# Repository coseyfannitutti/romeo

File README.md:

# ROMEO
 Staggered 40% QMK and VIA compatible keyboard pcb assembled with only through hole components, including USB Type-C

**[BOM, Build Guide, and Flashing Information](./doc)**

**Kits available at [cftkb.com](https://www.cftkb.com)**

**[Optional High Profile Lasercut Acrylic Case](./case)**

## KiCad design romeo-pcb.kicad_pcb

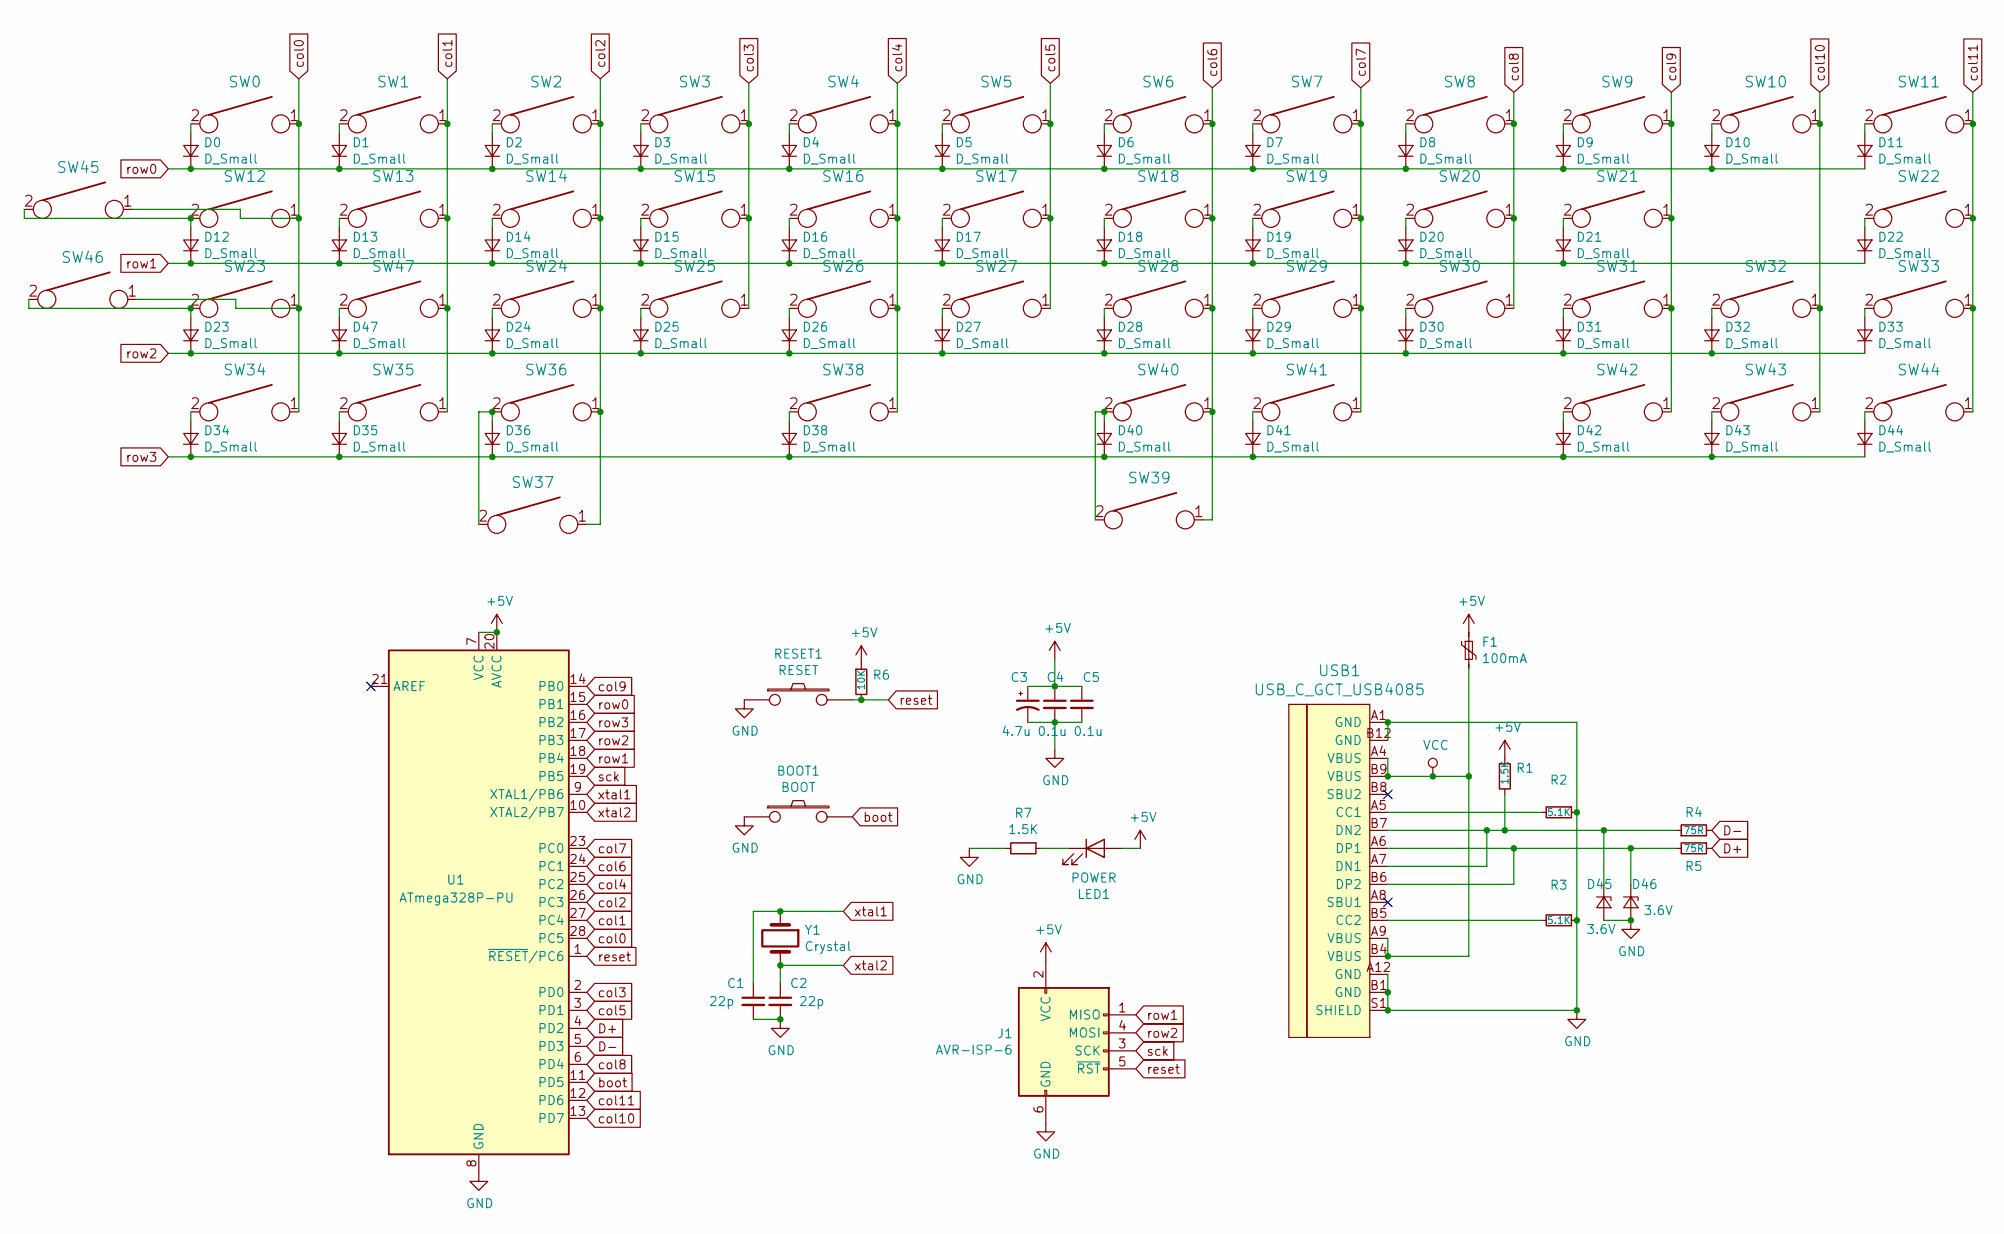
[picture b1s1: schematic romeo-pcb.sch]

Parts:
BOOT1: BOOT; SW_PUSH_6mm
C1, C2: 22p; C_Disc_D3.0mm_W1.6mm_P2.50mm
C3: 4.7u; CP_Radial_D4.0mm_P1.50mm
C4, C5: 0.1u; C_Disc_D4.3mm_W1.9mm_P5.00mm
D0, D1, D2, D3, D4, D5, D6, D7, D8, D9, D10, D11, D12, D13, D14, D15, D16, D17, D18, D19, D20, D21, D22, D23, D24, D25, D26, D27, D28, D29, D30, D31, D32, D33, D34, D35, D36, D38, D40, D41, D42, D43, D44, D47: D_Small; D_DO-35_SOD27_P5.08mm_Horizontal
D45, D46: 3.6V; D_DO-35_SOD27_P5.08mm_Horizontal
F1: 100mA; polyfuse_5.1mm
J1: AVR-ISP-6; AVR_ICSP_3x2
LED1: POWER; LED_D3.0mm
R1, R7: 1.5K; R_Axial_DIN0204_L3.6mm_D1.6mm_P5.08mm_Horizontal
R2, R3: 5.1K; R_Axial_DIN0204_L3.6mm_D1.6mm_P5.08mm_Horizontal
R4, R5: 75R; R_Axial_DIN0204_L3.6mm_D1.6mm_P5.08mm_Horizontal
R6: 10K; R_Axial_DIN0204_L3.6mm_D1.6mm_P5.08mm_Horizontal
RESET1: RESET; SW_PUSH_6mm
SW0, SW11: KEYSW; SW_Cherry_MX1A_1.50u_PCBNOSCREEN
SW1, SW2, SW3, SW4, SW5, SW6, SW7, SW8, SW9, SW10, SW13, SW14, SW15, SW16, SW17, SW18, SW19, SW20, SW21, SW24, SW25, SW26, SW27, SW28, SW29, SW30, SW31, SW32, SW35, SW36, SW39, SW40, SW43, SW47: KEYSW; SW_Cherry_MX1A_1.00u_PCB-NOSCREEN
SW12, SW33: KEYSW; SW_Cherry_MX1A_1.75u_PCBNOSCREEN
SW22, SW23, SW38: KEYSW; SW_Cherry_MX1A_2.25u_PCBNOSCREEN
SW34, SW37, SW42, SW44, SW45, SW46: KEYSW; SW_Cherry_MX1A_1.25u_PCBNOSCREEN
SW41: KEYSW; SW_Cherry_MX1A_2.75u_PCB_NOSCREEN
U1: ATmega328P-PU; DIP-28_W7.62mm
USB1: USB_C_GCT_USB4085
Y1: Crystal; Crystal_HC49-4H_Vertical

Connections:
+5V: C3.1, C4.1, C5.1, F1.1, J1.2 (VCC), LED1.2 (A), R1.1, R6.1, U1.7 (VCC), U1.20 (AVCC)
D+: R5.1, U1.4 (PD2)
D-: R4.2, U1.5 (PD3)
GND: BOOT1.1, C1.2, C2.2, C3.2, C4.2, C5.2, D45.2 (A), D46.2 (A), J1.6 (GND), R2.1, R3.1, R7.2, RESET1.1, U1.8 (GND), U1.22 (GND), USB1.A1 (GND), USB1.A12 (GND), USB1.B1 (GND), USB1.B12 (GND), USB1.S1 (SHIELD)
unnamed: D0.2 (A), SW0.2
unnamed: D1.2 (A), SW1.2
unnamed: D2.2 (A), SW2.2
unnamed: D3.2 (A), SW3.2
unnamed: D4.2 (A), SW4.2
unnamed: D5.2 (A), SW5.2
unnamed: D6.2 (A), SW6.2
unnamed: D7.2 (A), SW7.2
unnamed: D8.2 (A), SW8.2
unnamed: D9.2 (A), SW9.2
unnamed: D10.2 (A), SW10.2
unnamed: D11.2 (A), SW11.2
unnamed: D12.2 (A), SW12.2, SW45.2
unnamed: D13.2 (A), SW13.2
unnamed: D14.2 (A), SW14.2
unnamed: D15.2 (A), SW15.2
unnamed: D16.2 (A), SW16.2
unnamed: D17.2 (A), SW17.2
unnamed: D18.2 (A), SW18.2
unnamed: D19.2 (A), SW19.2
unnamed: D20.2 (A), SW20.2
unnamed: D21.2 (A), SW21.2
unnamed: D22.2 (A), SW22.2
unnamed: D23.2 (A), SW23.2, SW46.2
unnamed: D24.2 (A), SW24.2
unnamed: D25.2 (A), SW25.2
unnamed: D26.2 (A), SW26.2
unnamed: D27.2 (A), SW27.2
unnamed: D28.2 (A), SW28.2
unnamed: D29.2 (A), SW29.2
unnamed: D30.2 (A), SW30.2
unnamed: D31.2 (A), SW31.2
unnamed: D32.2 (A), SW32.2
unnamed: D33.2 (A), SW33.2
unnamed: D34.2 (A), SW34.2
unnamed: D35.2 (A), SW35.2
unnamed: D36.2 (A), SW36.2, SW37.2
unnamed: D38.2 (A), SW38.2
unnamed: D40.2 (A), SW39.2, SW40.2
unnamed: D41.2 (A), SW41.2
unnamed: D42.2 (A), SW42.2
unnamed: D43.2 (A), SW43.2
unnamed: D44.2 (A), SW44.2
unnamed: D45.1 (K), R1.2, R4.1, USB1.A7 (DN1), USB1.B7 (DN2)
unnamed: D46.1 (K), R5.2, USB1.A6 (DP1), USB1.B6 (DP2)
unnamed: D47.2 (A), SW47.2
unnamed: LED1.1 (K), R7.1
unnamed: R2.2, USB1.A5 (CC1)
unnamed: R3.2, USB1.B5 (CC2)
VCC: F1.2, USB1.A4 (VBUS), USB1.A9 (VBUS), USB1.B4 (VBUS), USB1.B9 (VBUS)
boot: BOOT1.2, U1.11 (PD5)
col0: SW0.1, SW12.1, SW23.1, SW34.1, SW45.1, SW46.1, U1.28 (PC5)
col1: SW1.1, SW13.1, SW35.1, SW47.1, U1.27 (PC4)
col2: SW2.1, SW14.1, SW24.1, SW36.1, SW37.1, U1.26 (PC3)
col3: SW3.1, SW15.1, SW25.1, U1.2 (PD0)
col4: SW4.1, SW16.1, SW26.1, SW38.1, U1.25 (PC2)
col5: SW5.1, SW17.1, SW27.1, U1.3 (PD1)
col6: SW6.1, SW18.1, SW28.1, SW39.1, SW40.1, U1.24 (PC1)
col7: SW7.1, SW19.1, SW29.1, SW41.1, U1.23 (PC0)
col8: SW8.1, SW20.1, SW30.1, U1.6 (PD4)
col9: SW9.1, SW21.1, SW31.1, SW42.1, U1.14 (PB0)
col10: SW10.1, SW32.1, SW43.1, U1.13 (PD7)
col11: SW11.1, SW22.1, SW33.1, SW44.1, U1.12 (PD6)
reset: J1.5 (~RST), R6.2, RESET1.2, U1.1 (~RESET~/PC6)
row0: D0.1 (K), D1.1 (K), D2.1 (K), D3.1 (K), D4.1 (K), D5.1 (K), D6.1 (K), D7.1 (K), D8.1 (K), D9.1 (K), D10.1 (K), D11.1 (K), U1.15 (PB1)
row1: D12.1 (K), D13.1 (K), D14.1 (K), D15.1 (K), D16.1 (K), D17.1 (K), D18.1 (K), D19.1 (K), D20.1 (K), D21.1 (K), D22.1 (K), J1.1 (MISO), U1.18 (PB4)
row2: D23.1 (K), D24.1 (K), D25.1 (K), D26.1 (K), D27.1 (K), D28.1 (K), D29.1 (K), D30.1 (K), D31.1 (K), D32.1 (K), D33.1 (K), D47.1 (K), J1.4 (MOSI), U1.17 (PB3)
row3: D34.1 (K), D35.1 (K), D36.1 (K), D38.1 (K), D40.1 (K), D41.1 (K), D42.1 (K), D43.1 (K), D44.1 (K), U1.16 (PB2)
sck: J1.3 (SCK), U1.19 (PB5)
xtal1: C1.1, U1.9 (XTAL1/PB6), Y1.1
xtal2: C2.1, U1.10 (XTAL2/PB7), Y1.2

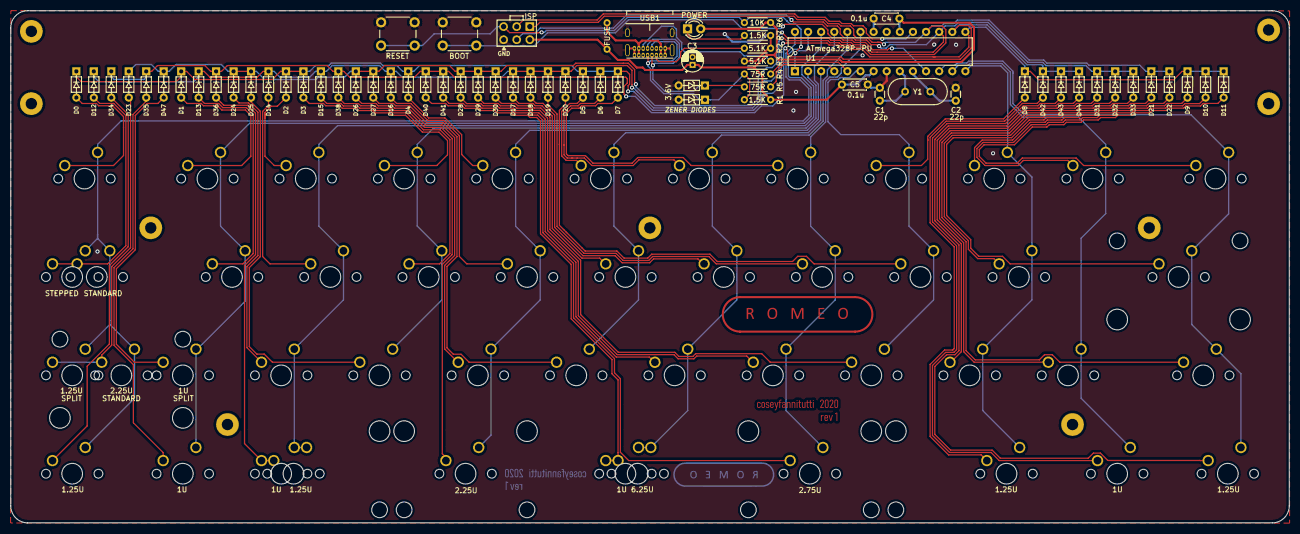
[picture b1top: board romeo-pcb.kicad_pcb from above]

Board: 2 copper layers, 247.6 x 99.2 mm, 115 parts (0 on the bottom side), 75 nets.

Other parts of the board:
ST39: 6.25U; MX-6.25U-Stabilizer

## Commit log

2019-11-02 Update fp-info-cache
2019-11-02 Update romeo-pcb.kicad_pcb-bak
2020-02-06 Update romeo-pcb.sch-bak
2020-03-20 Update PCB and add case files
2020-03-20 Consolidate gerber files
2020-04-04 fix scaling
2020-11-30 Update acrylic-guard.dxf
    fix scaling
